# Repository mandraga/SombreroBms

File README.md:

# SombreroBms

SombreroBMS could have been a battery management system board and software for small electric vehicles and conversions. Mainly 36V and 48V battery packs for golf carts.
Currently an unfinished project. Reading the sensors worked and monitoring from a serial line worked. The repository has a simulation project in order to try different balancing algorithms.

Planed features:

- Lithium phosphate battery packs.
- Protection relay to connect to a power relays like a Gigavac 250A.
- State of charge updated by a current sensor during the discharge.
- Custom gauge connected with one wire + Gnd serial communication.
- Monitoring from a laptop computer using a serial communication over USB.
- Passive balancing (possibility for a heavy duty version for first balancing use).
- Undervoltage events count per battery + worst value recording.
- Powered from the battery pack.
- 10 to 18 batteries.

The development was interrupted when I moved to Lyon in 2016. And the client switched to Orion BMS, so the target was lost and the funding shorted.
However I started SombreroBMS2, simpler, safer, cheaper and easier to use. For lighter vehicles (but it will keep the same functionnality).
I will add more unit testing and simulation on it (hence the switch to gitlab). Building more on software interfaces and abstraction layers and using the test driven development aproach.
On the second version the client is myself :)

https://gitlab.com/arenyp/sombrerobms2
http://blog.vreemdelabs.com/

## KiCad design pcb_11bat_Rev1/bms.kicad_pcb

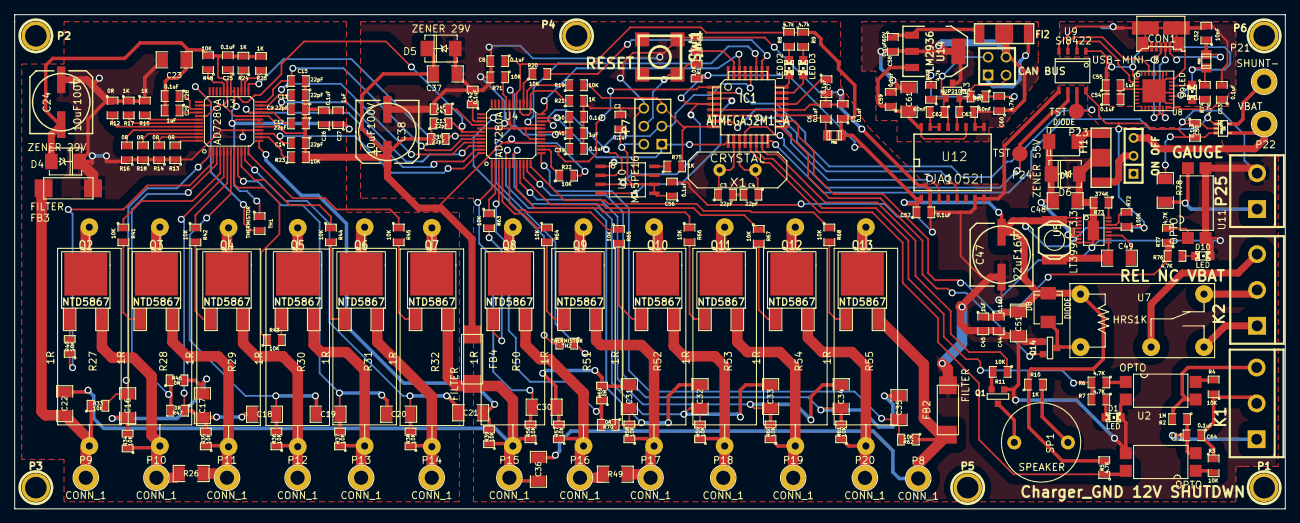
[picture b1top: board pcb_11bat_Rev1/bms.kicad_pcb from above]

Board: 2 copper layers, 180.0 x 70.0 mm, 225 parts (0 on the bottom side), 171 nets.

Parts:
C1, C2, C5, C6, C7, C8, C25, C26, C28, C39, C40, C42, C44, C50, C53, C54, C56, C57, C59, C64: 0.1uF; SM0805
C3, C4, C9, C10, C11, C12, C13, C14, C15: 22pF; SM0805
C16, C17, C18, C19, C20, C21, C30, C31, C32, C33, C34, C35: 0.1uF50V; SM1206
C22, C23, C36, C37: 0.1uF100V; SM1206
C24, C38: 10uF100V; SMDHD/VF
C27, C29, C41, C43, C45, C55: 1uF; SM0805
C47: 22uF16V; SMDHD/VF
C48: 2.2uF100V; SM1206
C49: 0.22uF100V; SM1206
C51: 10uF20V; SM1206POL
C52: 10nF; SM0805
C58: 0.1uF60V; SM0805
C60: 4,7nF; SM0805
C61: 3uF; SM1206
C62, C63: 60nF; SM0805
CAN BUS: CONN_4; PIN_ARRAY_2X2
CON1: USB-MINI-B; MICRO_USB_B
D1, D2, D3, D9, D10: LED; LED-0805
D4, D5: ZENER 29V; DO-214AA(SMB)
D6: ZENER 55V; DO-214AA(SMB)
D7, D8: DIODE; DO_214AA
FB1, FB5: FILTER; c_0805
FB2, FB3, FB4: FILTER; FILTER_NFE61HT102F
FI1, FI2: EMI_FILTER2; EMI_FILTER_NFE61HT
IC1: ATMEGA32M1-A; TQFP32
K1: Charger_GND 12V SHUTDWN; bornier3
K2: REL NC VBAT; bornier3
L1: 33µH; inductor-coilcraft-DS1608
ON OFF: SWITCH_INV; MICROSWITCH_SPST
P1, P2, P3, P4, P5, P6: CONN_1; 1pin
P7: CONN_3X2; pin_array_3x2
P8, P9, P10, P11, P12, P13, P14, P15, P16, P17, P18, P19, P20: CONN_1; 1pin2mm
P21: SHUNT-; 1pin2mm
P22: VBAT; 1pin2mm
P23, P24: TST; TestP
P25: GAUGE; bornier2
Q1, Q14: BC850; SOT23EBC
Q2, Q3, Q4, Q5, Q6, Q7, Q8, Q9, Q10, Q11, Q12, Q13: NTD5867; DPAK2
R1, R3, R4, R11, R19, R20, R22, R23, R33, R34, R35, R36, R37, R38, R39, R40, R41, R42, R43, R44, R45, R48, R56, R57, R58, R59, R60, R61, R62, R63, R64, R65, R66, R67, R68, R71: 10K; SM0805
R2: 1M; SM0805
R5, R6, R7: 4.7K; SM0805
R8, R9: 4.7k; SM0805
R10, R15, R17, R21, R24, R25, R75: 1K; SM0805
R12, R13, R14, R16, R18, R46, R47, R69, R70: 0R; SM0805
R26, R49: 0R; SM1206
R27, R28, R29, R30, R31, R32, R50, R51, R52, R53, R54, R55: 1R; POW_RES
R72: 100K; SM0805
R73: 374K; SM0805
R74, R76, R77: 4,7K; SM0805
R78: 10K; SM1206
R79, R80: 4,7k; SM0805
SP1: SPEAKER; buzzer
SW1: RESET; CMSSW
TH1, TH2: THERMISTOR; SM0805
U1, U2, U11: OPTO; OPTO_CMS
U3, U4: AD7280A; LQFP48
U5: LT3990-3.3; MSOP16E
U6: INA197; sot323-5
U7: HRS1K; REL_PE014
U8: FT232RQ; QFN32-5x5
U9: SI8422; NSOP8
U10: M45PE16; SO8W
U12: TJA1052I; SO16W
U13: NUP2105L; SOT23
U14: LM2936; SOT223
X1: CRYSTAL; HC-18UV

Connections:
/AD7280A/AD7280A_SUB_HI/ALERT: R24.1, U3.27
/AD7280A/AD7280A_SUB_HI/ALERT_IO: C13.2, U3.28, U4.42
/AD7280A/AD7280A_SUB_HI/ALERThi: R15.2, U3.42
/AD7280A/AD7280A_SUB_HI/CB1: R45.1, U3.12
/AD7280A/AD7280A_SUB_HI/CB2: R44.1, U3.10
/AD7280A/AD7280A_SUB_HI/CB3: R43.1, U3.8
/AD7280A/AD7280A_SUB_HI/CB4: R42.1, U3.6
/AD7280A/AD7280A_SUB_HI/CB5: R41.1, U3.4
/AD7280A/AD7280A_SUB_HI/CB6: R40.1, U3.2
/AD7280A/AD7280A_SUB_HI/CNVST/: C15.1, U3.24, U4.44
/AD7280A/AD7280A_SUB_HI/CNVSThi/: R12.2, U3.44
/AD7280A/AD7280A_SUB_HI/CRef: C28.1, U3.39
/AD7280A/AD7280A_SUB_HI/CS/: C12.2, U3.21, U4.47
/AD7280A/AD7280A_SUB_HI/CShi/: R14.2, U3.47
/AD7280A/AD7280A_SUB_HI/HIBAT: C22.1, FB3.1, P9.1, R27.1, R33.1
/AD7280A/AD7280A_SUB_HI/MASTER: R23.1, U3.14
/AD7280A/AD7280A_SUB_HI/PD/: C14.2, U3.15, U4.48
/AD7280A/AD7280A_SUB_HI/PDhi/: R13.2, U3.48
/AD7280A/AD7280A_SUB_HI/SCLK: C9.2, U3.22, U4.46
/AD7280A/AD7280A_SUB_HI/SCLKhi: R18.2, U3.46
/AD7280A/AD7280A_SUB_HI/SDI: C11.2, U3.23, U4.45
/AD7280A/AD7280A_SUB_HI/SDIhi: R17.2, U3.43
/AD7280A/AD7280A_SUB_HI/SDO: R25.1, U3.26
/AD7280A/AD7280A_SUB_HI/SDOhi: R16.2, U3.45
/AD7280A/AD7280A_SUB_HI/VDDNFILTERED: C23.1, C24.1, D4.2, FB3.2, R12.1, R13.1, R14.1, R15.1, R16.1, R17.1, R18.1, U3.16
/AD7280A/AD7280A_SUB_HI/VDRIVE: C25.1, C26.1, C27.1, TH1.1, U3.18, U3.19, U3.29, U3.30
/AD7280A/AD7280A_SUB_HI/VIN0: C21.2, R39.2, U3.13
/AD7280A/AD7280A_SUB_HI/VIN1: C20.2, C21.1, R38.2, U3.11
/AD7280A/AD7280A_SUB_HI/VIN2: C19.2, C20.1, R37.2, U3.9
/AD7280A/AD7280A_SUB_HI/VIN3: C18.2, C19.1, R36.2, U3.7
/AD7280A/AD7280A_SUB_HI/VIN4: C17.2, C18.1, R35.2, R47.1, U3.5
/AD7280A/AD7280A_SUB_HI/VIN5: R46.1, R47.2, U3.3
/AD7280A/AD7280A_SUB_HI/VIN6: C16.1, R33.2, U3.1
/AD7280A/AD7280A_SUB_HI/VRef: C29.1, U3.40
/AD7280A/AD7280A_SUB_LO/ALERT: R20.1, U4.27
/AD7280A/AD7280A_SUB_LO/ALERT_IO: R21.1, U4.25, U4.28
/AD7280A/AD7280A_SUB_LO/CB1: R68.1, U4.12
/AD7280A/AD7280A_SUB_LO/CB2: R67.1, U4.10
/AD7280A/AD7280A_SUB_LO/CB3: R66.1, U4.8
/AD7280A/AD7280A_SUB_LO/CB4: R65.1, U4.6
/AD7280A/AD7280A_SUB_LO/CB5: R64.1, U4.4
/AD7280A/AD7280A_SUB_LO/CB6: R63.1, U4.2
/AD7280A/AD7280A_SUB_LO/CRef: C42.1, U4.39
/AD7280A/AD7280A_SUB_LO/HIBAT: C22.2, C36.1, FB4.1, P15.1, Q7.3, R39.1, R50.1, R56.1
/AD7280A/AD7280A_SUB_LO/LOBAT: C36.2, FB2.2, P8.1, Q13.3, R62.1
/AD7280A/AD7280A_SUB_LO/MASTER: R22.1, U4.14
/AD7280A/AD7280A_SUB_LO/SDIhi: C10.2, U3.25, U4.43
/AD7280A/AD7280A_SUB_LO/SDO: R19.1, U4.26
/AD7280A/AD7280A_SUB_LO/VDDNFILTERED: C9.1, C10.1, C11.1, C12.1, C13.1, C14.1, C15.2, C23.2, C24.2, C25.2, C26.2, C27.2, C28.2, C29.2, C37.1, C38.1, D4.1, D5.2, FB4.2, R22.2, R23.2, R24.2, R25.2, R48.2, U3.17, U3.20, U3.31, U3.41, U4.16
/AD7280A/AD7280A_SUB_LO/VIN0: C35.2, R62.2, U4.13
/AD7280A/AD7280A_SUB_LO/VIN1: C34.2, C35.1, R61.2, U4.11
/AD7280A/AD7280A_SUB_LO/VIN2: C33.2, C34.1, R60.2, U4.9
/AD7280A/AD7280A_SUB_LO/VIN3: C32.2, C33.1, R59.2, U4.7
/AD7280A/AD7280A_SUB_LO/VIN4: C31.2, C32.1, R58.2, R70.1, U4.5
/AD7280A/AD7280A_SUB_LO/VIN5: R69.1, R70.2, U4.3
/AD7280A/AD7280A_SUB_LO/VIN6: C30.1, R56.2, U4.1
/AD7280A/AD7280A_SUB_LO/VREG: C39.1, C40.1, C41.1, TH2.1, U4.18, U4.19, U4.30
/AD7280A/AD7280A_SUB_LO/VRef: C43.1, U4.40
/AD7280A/ALERT: IC1.26, R20.2
/AD7280A/CNVST/: IC1.30, U4.24
/AD7280A/CS/: IC1.27, U4.21
/AD7280A/PD/: IC1.1, U4.15
/AD7280A/SDI: IC1.9, P7.1, U4.23, U10.1
/AD7280A/SDO: IC1.8, P7.5, R19.2, R75.2
/BUZZER: IC1.15, R11.1
/CHARGER_12V: C64.1, K1.2, R3.1, R4.1
/CHARGER_GND: C64.2, K1.1, R2.1, U1.2
/CHARGER_ON/: IC1.13, R5.1, U1.4
/CLK1: C3.1, IC1.10, X1.2
/CLK2: C4.1, IC1.11, X1.1
/CSense/CSENSE: IC1.16, U6.1
/CSense/SHUNT-: P21.1, U6.5
/CSense/VBAT: ON OFF.3, P22.1, U6.4
/Gauge/GAUGEOUT: IC1.18, R76.1, R77.1
/Gauge/GaugeValue: P25.1, R78.2, U11.4
/Isolated_CAN/BMSCANRX: IC1.7, U12.5
/Isolated_CAN/BMSCANTX: IC1.6, U12.3
/Isolated_CAN/BMSGND: C1.2, C2.2, C3.2, C4.2, C5.2, C6.2, C7.2, C8.2, C37.2, C38.2, C39.2, C40.2, C41.2, C42.2, C43.2, C44.2, C45.2, C47.2, C48.2, C50.1, C51.2, C56.2, C57.2, D1.2, D5.1, D6.1, D10.2, FB2.1, FI1.2, IC1.5, IC1.20, P7.6, P25.2, Q1.2, Q14.2, R21.2, R71.2, R73.2, SW1.2, U1.3, U2.2, U4.17, U4.20, U4.31, U4.41, U5.8, U5.17, U6.2, U9.5, U10.7, U11.2, U11.3, U12.2, U12.7, U12.8
/Isolated_CAN/CAN12V: C58.1, FI2.1, U14.1
/Isolated_CAN/CANGND: C58.2, C59.2, C60.1, C61.2, C62.2, C63.1, CAN BUS.4, FI2.2, U12.9, U12.10, U12.14, U12.15, U13.3, U14.2, U14.4
/Isolated_CAN/CANH: C62.1, CAN BUS.2, R79.1, U12.13, U13.1
/Isolated_CAN/CANL: C63.2, CAN BUS.3, R80.2, U12.12, U13.2
/Isolated_CAN/CANUNFILTERED12V: CAN BUS.1, FI2.3
/Isolated_CAN/CANVDD: C59.1, C61.1, U12.11, U12.16, U14.3
/LEDBALANCING: D3.2, IC1.23
/LEDERROR: D2.2, IC1.24
/RESET/: C1.1, IC1.31, P7.4, R1.1, SW1.1
/SPI Flash/CLK: IC1.28, P7.3, U4.22, U10.2
/SPI Flash/CSFLASH/: IC1.3, U10.4
/SPI Flash/FSDO: R75.1, U10.8
/STOP_CHARGE: K1.3, R2.2, U2.3
/STOP_CHARGER: IC1.14, R6.2, R7.2
/VREG/3.3V: C2.1, C5.1, C8.1, C44.1, C45.1, C47.1, C50.2, C51.1, C56.1, C57.1, D8.2, FB1.2, IC1.4, L1.1, P7.2, R1.2, R5.2, R8.1, R9.1, R10.1, R72.1, R78.1, U4.29, U5.1, U5.2, U5.13, U6.3, U7.1, U9.8, U10.3, U10.5, U10.6, U12.1
/VREG/PG: R72.2, U5.14
/VREG/SW: C49.2, L1.2, U5.9
/VREG/VIN: C48.1, D6.2, D7.2, U5.4, U5.6
/comandsolenoid/COILON: IC1.17, Q14.1
/comandsolenoid/StartCOIL: K2.1, U7.4
/comandsolenoid/VbatCOIL: K2.3, U7.3
/usbserial/3V3OUT: C53.1, U8.16
/usbserial/RXD: IC1.12, P24.1, U9.6
/usbserial/TXD: IC1.2, P23.1, U9.7
/usbserial/USBGND: C52.2, C53.2, C54.2, C55.2, CON1.5, CON1.6, CON1.7, CON1.8, CON1.9, U8.4, U8.17, U8.20, U8.24, U8.26, U8.33, U9.4
/usbserial/USBVCC: C54.1, C55.1, FB5.2, R74.1, U8.1, U8.19, U9.1
unnamed: R10.2, SP1.1
unnamed: Q1.3, SP1.2
unnamed: Q1.1, R11.2
unnamed: D3.1, R9.2
unnamed: D2.1, R8.2
unnamed: C7.1, IC1.21
unnamed: D1.1, R7.1
unnamed: R3.2, U1.1
unnamed: R6.1, U2.1
unnamed: C6.1, FB1.1, IC1.19
unnamed: R4.2, U2.4
unnamed: C49.1, U5.11
unnamed: FI1.3, ON OFF.2
unnamed: R73.1, U5.16
unnamed: D7.1, FI1.1
unnamed: K2.2, U7.5
unnamed: D8.1, Q14.3, U7.2
unnamed: D9.2, U8.22
unnamed: CON1.3, U8.14
unnamed: CON1.2, U8.15
unnamed: C52.1, CON1.1, FB5.1
unnamed: D9.1, R74.2
unnamed: U8.30, U9.3
unnamed: U8.2, U9.2
unnamed: D10.1, R76.2
unnamed: R77.2, U11.1
unnamed: C60.2, R79.2, R80.1
unnamed: R48.1, U3.32
unnamed: TH1.2, U3.38
unnamed: Q5.1, R43.2
unnamed: P13.1, Q5.3, R31.1, R37.1
unnamed: Q5.2, R30.2
unnamed: Q4.1, R42.2
unnamed: P12.1, Q4.3, R30.1, R36.1
unnamed: Q4.2, R29.2
unnamed: Q7.1, R45.2
unnamed: Q7.2, R32.2
unnamed: Q6.1, R44.2
unnamed: P14.1, Q6.3, R32.1, R38.1
unnamed: Q6.2, R31.2
unnamed: Q2.2, R27.2
unnamed: Q3.2, R28.2
unnamed: P11.1, Q3.3, R26.2, R29.1, R35.1
unnamed: Q3.1, R41.2
unnamed: Q2.1, R40.2
unnamed: C16.2, C17.1, R34.2, R46.2
unnamed: P10.1, Q2.3, R26.1, R28.1, R34.1
unnamed: R71.1, U4.32
unnamed: TH2.2, U4.38
unnamed: Q13.1, R68.2
unnamed: Q12.1, R67.2
unnamed: Q11.1, R66.2
unnamed: Q10.1, R65.2
unnamed: Q9.1, R64.2
unnamed: Q8.1, R63.2
unnamed: Q9.2, R51.2
unnamed: Q10.2, R52.2
unnamed: P18.1, Q10.3, R53.1, R59.1
unnamed: Q11.2, R53.2
unnamed: Q8.2, R50.2
unnamed: P19.1, Q11.3, R54.1, R60.1
unnamed: Q12.2, R54.2
unnamed: P20.1, Q12.3, R55.1, R61.1
unnamed: Q13.2, R55.2
unnamed: C30.2, C31.1, R57.2, R69.2
unnamed: P16.1, Q8.3, R49.1, R51.1, R57.1
unnamed: P17.1, Q9.3, R49.2, R52.1, R58.1

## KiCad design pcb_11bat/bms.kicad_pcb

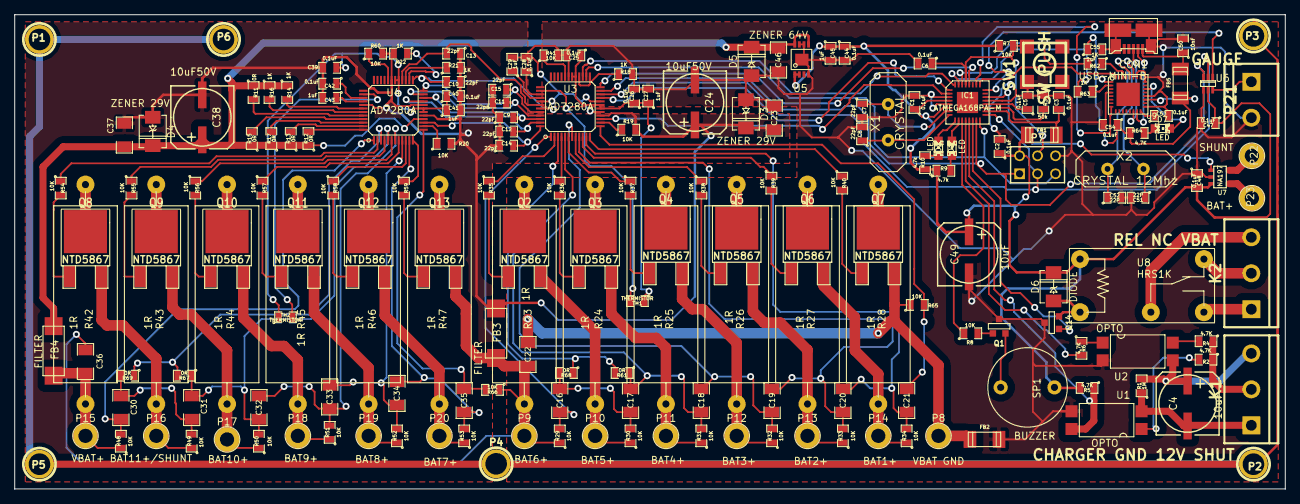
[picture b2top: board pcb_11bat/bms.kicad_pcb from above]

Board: 2 copper layers, 179.5 x 67.0 mm, 192 parts (0 on the bottom side), 152 nets.

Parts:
C1, C2, C3, C5, C6, C25, C26, C28, C39, C40, C42, C44, C47, C48, C53, C54: 0.1uF; SM0805
C4, C49: 10uF; SMDHD/VF
C7, C8, C9, C10, C11, C12, C13, C14, C15: 22pF; SM0805
C16, C17, C18, C19, C20, C21, C22, C23, C30, C31, C32, C33, C34, C35, C36, C37: 0.1uF50V; SM1206
C24, C38: 10uF50V; SMDHD/VF
C27, C29, C41, C43, C45, C55: 1uF; SM0805
C46: 1uF50V; SM1206
C50: 10nF; SM0805
C51, C52: 22P; SM0805
CON1: USB-MINI-B; MICRO_USB_B
D1, D2, D7: LED; LED-0805
D3, D4: ZENER 29V; DO-214AA(SMB)
D5: ZENER 64V; DO-214AA(SMB)
D6: DIODE; DO-214AA(SMB)
FB1, FB2, FB5: FILTER; c_1808
FB3, FB4: FILTER; FILTER_NFE61HT102F
IC1: ATMEGA168PA-M; QFN32
K1: CHARGER GND 12V SHUT; bornier3
K2: REL NC VBAT; bornier3
P1, P2, P3, P4, P5, P6: CONN_1; 1pin
P7: CONN_3X2; pin_array_3x2
P8: VBAT GND; 1pin2mm
P9: BAT6+; 1pin2mm
P10: BAT5+; 1pin2mm
P11: BAT4+; 1pin2mm
P12: BAT3+; 1pin2mm
P13: BAT2+; 1pin2mm
P14: BAT1+; 1pin2mm
P15: VBAT+; 1pin2mm
P16: BAT11+/SHUNT; 1pin2mm
P17: BAT10+; 1pin2mm
P18: BAT9+; 1pin2mm
P19: BAT8+; 1pin2mm
P20: BAT7+; 1pin2mm
P21: GAUGE; bornier2
P22: SHUNT; 1pin2mm
P23: BAT+; 1pin2mm
Q1, Q14: BC550; SOT23EBC
Q2, Q3, Q4, Q5, Q6, Q7, Q8, Q9, Q10, Q11, Q12, Q13: NTD5867; DPAK2
R1: 1M; SM0805
R2, R4, R5, R6: 4.7K; SM0805
R3: 50k; SM0805
R7, R8, R19, R20, R29, R30, R31, R32, R33, R34, R35, R36, R37, R38, R39, R40, R41, R48, R49, R50, R51, R52, R53, R54, R55, R56, R57, R58, R59, R60, R65, R66: 10K; SM0805
R9, R10: 4.7k; SM0805
R11, R12, R13, R15, R17, R61, R67, R68, R69: 0R; SM0805
R14, R16, R18, R21, R22, R62, R63: 1K; SM0805
R23, R24, R25, R26, R27, R28, R42, R43, R44, R45, R46, R47: 1R; POW_RES
R64: 4,7K; SM0805
SP1: BUZZER; buzzer
SW1: SW_PUSH; CMSSW
TH1, TH2: THERMISTOR; SM0805
U1, U2: OPTO; OPTO_CMS
U3, U4: AD7280A; LQFP48
U5: LT3010-5; MSOP8E
U6: LTC2630; SC6
U7: INA197; SOT23-5
U8: HRS1K; REL_PE014
U9: FT232RQ; QFN32-5x5
X1: CRYSTAL; HC-18UV
X2: CRYSTAL 12Mhz; HC-18UV

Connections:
/AD7280A/AD7280A_SUB_HI/ALERT: R21.1, U4.27
/AD7280A/AD7280A_SUB_HI/ALERT_IO: C13.2, U3.42, U4.28
/AD7280A/AD7280A_SUB_HI/ALERThi: R14.2, U4.42
/AD7280A/AD7280A_SUB_HI/AO5.2V: C39.1, C40.1, C41.1, TH2.1, U4.18, U4.19, U4.29, U4.30
/AD7280A/AD7280A_SUB_HI/CB1: R59.1, U4.12
/AD7280A/AD7280A_SUB_HI/CB2: R58.1, U4.10
/AD7280A/AD7280A_SUB_HI/CB3: R57.1, U4.8
/AD7280A/AD7280A_SUB_HI/CB4: R56.1, U4.6
/AD7280A/AD7280A_SUB_HI/CB5: R55.1, U4.4
/AD7280A/AD7280A_SUB_HI/CB6: R54.1, U4.2
/AD7280A/AD7280A_SUB_HI/CNVST/: C15.1, U3.44, U4.24
/AD7280A/AD7280A_SUB_HI/CNVSThi/: R11.2, U4.44
/AD7280A/AD7280A_SUB_HI/CRef: C42.1, U4.39
/AD7280A/AD7280A_SUB_HI/CS/: C12.2, U3.47, U4.21
/AD7280A/AD7280A_SUB_HI/CShi/: R13.2, U4.47
/AD7280A/AD7280A_SUB_HI/HIBAT: C36.1, FB4.1, P15.1, R42.1, R48.1
/AD7280A/AD7280A_SUB_HI/MASTER: R20.1, U4.14
/AD7280A/AD7280A_SUB_HI/PD/: C14.2, U3.48, U4.15
/AD7280A/AD7280A_SUB_HI/PDhi/: R12.2, U4.48
/AD7280A/AD7280A_SUB_HI/SCLK: C9.2, U3.46, U4.22
/AD7280A/AD7280A_SUB_HI/SCLKhi: R17.2, U4.46
/AD7280A/AD7280A_SUB_HI/SDI: C11.2, U3.45, U4.23
/AD7280A/AD7280A_SUB_HI/SDIhi: R16.2, U4.43
/AD7280A/AD7280A_SUB_HI/SDO: R22.1, U4.26
/AD7280A/AD7280A_SUB_HI/SDOhi: R15.2, U4.45
/AD7280A/AD7280A_SUB_HI/VIN0: C35.2, R66.2, U4.13
/AD7280A/AD7280A_SUB_HI/VIN1: C34.2, C35.1, R53.2, U4.11
/AD7280A/AD7280A_SUB_HI/VIN2: C33.2, C34.1, R52.2, U4.9
/AD7280A/AD7280A_SUB_HI/VIN3: C32.2, C33.1, R51.2, U4.7
/AD7280A/AD7280A_SUB_HI/VIN4: C31.2, C32.1, R50.2, R67.1, U4.5
/AD7280A/AD7280A_SUB_HI/VIN5: R67.2, R69.1, U4.3
/AD7280A/AD7280A_SUB_HI/VIN6: C30.1, R48.2, U4.1
/AD7280A/AD7280A_SUB_HI/VRef: C43.1, U4.40
/AD7280A/AD7280A_SUB_LOW/ALERT_IO: R18.1, U3.25, U3.28
/AD7280A/AD7280A_SUB_LOW/AO5.2V: C25.1, C26.1, C27.1, TH1.1, U3.18, U3.19, U3.29, U3.30
/AD7280A/AD7280A_SUB_LOW/CB1: R40.1, U3.12
/AD7280A/AD7280A_SUB_LOW/CB2: R39.1, U3.10
/AD7280A/AD7280A_SUB_LOW/CB3: R38.1, U3.8
/AD7280A/AD7280A_SUB_LOW/CB4: R37.1, U3.6
/AD7280A/AD7280A_SUB_LOW/CB5: R36.1, U3.4
/AD7280A/AD7280A_SUB_LOW/CB6: R35.1, U3.2
/AD7280A/AD7280A_SUB_LOW/CRef: C28.1, U3.39
/AD7280A/AD7280A_SUB_LOW/HIBAT: C22.1, C36.2, FB3.1, P9.1, Q13.3, R23.1, R29.1, R66.1
/AD7280A/AD7280A_SUB_LOW/LOBAT: C22.2, FB2.2, P8.1, Q7.3, R65.1
/AD7280A/AD7280A_SUB_LOW/MASTER: R19.1, U3.14
/AD7280A/AD7280A_SUB_LOW/SDIhi: C10.2, U3.43, U4.25
/AD7280A/AD7280A_SUB_LOW/VDDNFILTERED: C9.1, C10.1, C11.1, C12.1, C13.1, C14.1, C15.2, C23.1, C24.1, C37.2, C38.2, C39.2, C40.2, C41.2, C42.2, C43.2, D3.2, D4.1, FB3.2, R19.2, R20.2, R21.2, R22.2, R60.2, U3.16, U4.17, U4.20, U4.31, U4.41
/AD7280A/AD7280A_SUB_LOW/VIN0: C21.2, R65.2, U3.13
/AD7280A/AD7280A_SUB_LOW/VIN1: C20.2, C21.1, R34.2, U3.11
/AD7280A/AD7280A_SUB_LOW/VIN2: C19.2, C20.1, R33.2, U3.9
/AD7280A/AD7280A_SUB_LOW/VIN3: C18.2, C19.1, R32.2, U3.7
/AD7280A/AD7280A_SUB_LOW/VIN4: C17.2, C18.1, R31.2, R61.1, U3.5
/AD7280A/AD7280A_SUB_LOW/VIN5: R61.2, R68.1, U3.3
/AD7280A/AD7280A_SUB_LOW/VIN6: C16.1, R29.2, U3.1
/AD7280A/AD7280A_SUB_LOW/VRef: C29.1, U3.40
/AD7280A/ALERT: IC1.32, U3.27
/AD7280A/CNVST/: IC1.28, U3.24
/AD7280A/CS/: IC1.1, U3.21
/AD7280A/GND: C1.2, C2.2, C3.2, C5.2, C6.2, C7.2, C8.2, C23.2, C24.2, C25.2, C26.2, C27.2, C28.2, C29.2, C44.2, C45.2, C46.2, C47.2, C48.1, C49.2, C50.2, C51.2, C52.2, C53.2, C54.2, C55.2, CON1.5, CON1.6, CON1.7, CON1.8, CON1.9, D3.1, D5.1, FB2.1, IC1.3, IC1.5, IC1.21, P7.6, P21.2, Q1.3, Q14.3, R3.1, R18.2, R41.2, SW1.2, U1.3, U2.2, U3.17, U3.20, U3.31, U3.41, U5.4, U5.6, U5.7, U5.9, U6.4, U7.2, U9.4, U9.17, U9.20, U9.24, U9.26
/AD7280A/PD/: IC1.2, U3.15
/AD7280A/SCLK: IC1.17, P7.3, U3.22, U6.2
/AD7280A/SDI: IC1.15, P7.1, U3.23, U6.3
/AD7280A/SDO: IC1.16, P7.5, U3.26
/AD7280A/VBAT: C37.1, C38.1, C46.1, D4.2, D5.2, FB4.2, R11.1, R12.1, R13.1, R14.1, R15.1, R16.1, R17.1, U4.16, U5.5, U5.8
/BUZZER: IC1.11, R8.1
/CHARGER_12V: K1.2, R2.1, R4.1
/CHARGER_GND: C4.2, K1.1, R1.1, U1.2
/CHARGER_ON/: IC1.13, R5.1, U1.4
/CSense/5V: C1.1, C2.1, C44.1, C45.1, C47.1, C48.2, C49.1, D6.2, FB1.2, IC1.4, IC1.6, P7.2, R5.2, R7.1, R9.1, R10.1, SP1.1, U5.1, U5.2, U6.5, U7.3, U8.1
/CSense/CSENSE: IC1.22, U7.1
/CSense/SHUNT-: P22.1, U7.5
/CSense/SHUNT_VBAT+: P23.1, U7.4
/LEDBALANCING: D2.2, IC1.9
/LEDERROR: D1.2, IC1.10
/RESET/: C6.1, IC1.29, P7.4, R7.2, SW1.1
/SHIELD: P1.1, P2.1, P3.1, P4.1, P5.1, P6.1
/STOP_CHARGE: C4.1, K1.3, R1.2, U2.3
/STOP_CHARGER: IC1.12, R6.2
/comandsolenoid/COILON: IC1.14, Q14.2
/comandsolenoid/StartCOIL: K2.1, U8.4
/comandsolenoid/VbatCOIL: K2.3, U8.3
/gauge/CSDAC/: IC1.24, U6.1
/gauge/GaugeValue: P21.1, U6.6
/usbserial/3V3OUT: C53.1, U9.16
/usbserial/CLEARTOSEND: IC1.26, U9.8
/usbserial/REQUESTTOSEND: IC1.25, U9.32
/usbserial/RXD: IC1.30, R62.2
/usbserial/TXD: IC1.31, R63.2
/usbserial/USBVCC: C54.1, C55.1, FB5.2, R64.1, U9.1, U9.19
unnamed: R6.1, U2.1
unnamed: R4.2, U2.4
unnamed: R2.2, U1.1
unnamed: Q1.1, SP1.2
unnamed: Q1.2, R8.2
unnamed: IC1.19, R3.2
unnamed: C3.1, FB1.1, IC1.18
unnamed: C5.1, IC1.20
unnamed: D2.1, R10.2
unnamed: D1.1, R9.2
unnamed: C7.1, IC1.7, X1.2
unnamed: C8.1, IC1.8, X1.1
unnamed: D6.1, Q14.1, U8.2
unnamed: K2.2, U8.5
unnamed: CON1.2, U9.15
unnamed: CON1.3, U9.14
unnamed: D7.2, U9.22
unnamed: C52.1, U9.28, X2.1
unnamed: R63.1, U9.2
unnamed: R62.1, U9.30
unnamed: C51.1, U9.27, X2.2
unnamed: D7.1, R64.2
unnamed: C50.1, CON1.1, FB5.1
unnamed: Q4.1, R37.2
unnamed: Q4.2, R25.2
unnamed: Q3.1, R36.2
unnamed: P11.1, Q3.3, R25.1, R31.1
unnamed: Q3.2, R24.2
unnamed: Q6.2, R27.2
unnamed: Q5.1, R38.2
unnamed: P13.1, Q5.3, R27.1, R33.1
unnamed: Q5.2, R26.2
unnamed: P12.1, Q4.3, R26.1, R32.1
unnamed: P10.1, Q2.3, R24.1, R30.1
unnamed: Q2.1, R35.2
unnamed: Q2.2, R23.2
unnamed: R41.1, U3.32
unnamed: TH1.2, U3.38
unnamed: Q7.1, R40.2
unnamed: Q7.2, R28.2
unnamed: Q6.1, R39.2
unnamed: P14.1, Q6.3, R28.1, R34.1
unnamed: C16.2, C17.1, R30.2, R68.2
unnamed: TH2.2, U4.38
unnamed: Q13.1, R59.2
unnamed: Q8.1, R54.2
unnamed: Q8.2, R42.2
unnamed: Q11.2, R45.2
unnamed: Q12.1, R58.2
unnamed: Q9.2, R43.2
unnamed: Q9.1, R55.2
unnamed: Q10.2, R44.2
unnamed: Q10.1, R56.2
unnamed: R60.1, U4.32
unnamed: Q13.2, R47.2
unnamed: P20.1, Q12.3, R47.1, R53.1
unnamed: Q12.2, R46.2
unnamed: C30.2, C31.1, R49.2, R69.2
unnamed: P16.1, Q8.3, R43.1, R49.1
unnamed: P17.1, Q9.3, R44.1, R50.1
unnamed: Q11.1, R57.2
unnamed: P18.1, Q10.3, R45.1, R51.1
unnamed: P19.1, Q11.3, R46.1, R52.1

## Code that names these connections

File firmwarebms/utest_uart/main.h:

#define SBI(port, bit) ((port) |= (1 << (bit)))
#define CBI(port, bit) ((port) &= ~(1 << (bit)))

// PORTB
#define CSBAT  PB0
#define BUZZER PB1
#define PD     PB2
#define MOSI   PB3
#define MISO   PB4
#define SCLK   PB5
#define OSC1   PB6
#define OSC2   PB7

// PORTC
#define CNVSTART  PC0
#define NC1       PC1
#define NC2       PC2
#define RTS       PC3
#define CTS       PC4
#define RELON     PC5
#define RESET     PC6

// PORTD
#define RXD           PD0
#define TXD           PD1
#define ALERT         PD2
#define CHARGER_ON    PD3
#define CSDAC         PD4
#define STOP_CHARGER  PD5
#define LED_BALANCING PD6
#define LED_ERROR     PD7

// Main state machine
#define STATE_START    0
#define STATE_CHARGEON 1  // The charger is on
#define STATE_CHARGING 2  // same plus charging
#define STATE_IDLE     3  // Idle, does nothing
#define STATE_RUN      4  // Run, the current is beingused and state of charge updated
#define STATE_RELAX    5  // After run, wait for the battery voltage to spatbilise (lithium behaviour)
#define STATE_SECURITY 6  // Undervoltage or overvoltage or error like trying to start when charging
#define STATE_CURRENT_SECURITY 7  // Over current or too much current during charge
#define STATE_CRITICAL_FAILURE 8  // Stops here, no way to get out but a reset

#define BAUDRATE       9600
#ifndef F_CPU
#define F_CPU       3686000
#endif

void _delay_ms_S(int millisecond);

typedef struct  s_ibat
{
  unsigned long ibat; // milliAmps
  int           timeslice_ms;
}               t_ibat;

// EEPROM data
typedef struct  s_eeprom_data
{
  int           install_date_year;
  char          install_date_month;
  char          install_date_day;
  unsigned long bat_maxv;            // mV
  unsigned long bat_minv;
  int           bat_tmax;            // temperature °C
  int           bat_tmin;
  char          bat_elements;
  int           full_charge;         // AH
  unsigned long full_chargeV;        // mV when the pack voltage reaches this value, the charger is stoped and the charge is set at 100%
  int           max_current;         // Amp
  char          serial_number[10];   //  8 bytes             plus 0 end of string
  char          client[33];          // 32 bytes Client name plus 0 end of string
  // These are often programmed
  int           charge_cycles;
  unsigned long charge_time_minutes; // Total charging time
  int           min_temperature;     // Extreme temperatures °C
  int           max_temperature;
}               t_eeprom_data;

// Per battery eeprom information
typedef struct  s_eeprom_battery
{
  unsigned long lowestV;
  int           lowVevents; // times vbat whent under the treshold before a charge
  unsigned long cap;        // More or less the capacity, or charge speed...
}               t_eeprom_battery;

// Ram data
typedef struct  s_pack_variable_data
{
  unsigned int  uptime_days;
  unsigned int  uptime_minutes;
  unsigned int  tseconds;                 // Tenth of seconds
  int           max_discharge;            // Discharge current in Amperes
  unsigned long c_discharge;              // Discharge, last value mA
  unsigned int  state_of_charge;          // SOC mili Ampere Hour
  unsigned long vbat[MAXBATTERY];         // Batterey milivolts, last value
  unsigned long total_vbat;               // Pack voltage in mv
  int           temperature[MAXMODULES];  // °C
  char          app_state;                // State machine variable
  // Internal variables
  unsigned long c_discharge_accumulator;  // Accumulates mA per hour
  char          charging_started;         // Once started it must finish
  int           charge_time_count_tenth;  // 1/10 second
  int           charge_time_count;        // Minutes
  int           idle_counter;             // Used to get out of the relapse state
  char          prev_idle;                // Used to count the charge cycles
}               t_pack_variable_data;

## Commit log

2015-11-21 Kicad schematics
2015-11-21 Kicad modules n libs
2016-01-03 Component association finished, added/created required modules
2016-01-03 changed wire pins to 2mm holes, mosfet NTD5867 shcematics and filter footprint, created the pcb file for routing
2016-01-04 placement before routing & corrected a missing resitor on vlow
2016-01-05 fixed misplaced caps on the vins, changed some pins assignations on the avr and routed
2016-01-06 sent to production, buzeer pad drill change, changed vias diameter
2016-01-21 Began to work on hte firmware
2016-01-22 added the begin of the state machine
2016-01-22 added a gitignore file
2016-01-23 changed the uart code to custom interrupt based code, and began to work on the rs232 protocol and eeprom writes
2016-01-24 finished to write the serial protocol and eeprom code, starting with the cell readings.
2016-01-25 basic features written, before the battery balancing algorithm
2016-01-25 started the balancing, added temperature and balancing state to the serial data specifications
2016-01-26 added the thermistor code, and finished the basics for battery balancing
2016-01-26 Added missing values to the serial code.
2016-01-27 compiled
2016-01-27 pushed the string constants into program space
2016-01-27 added simulation code and compiled the bootloader
2016-01-28 first working version on the simulator
2016-01-29 balancing works on the simulator
2016-02-08 Soldering components on the prototype, some changes on the schematics and component values
2016-02-11 added PC side FLTX inteface, plus named pipe serial suport to be used in the simulator
2016-02-12 added the serial port tab, untested
2016-02-12 commit just to store the code before returning to scoreview
2016-02-25 changed the board to add an SPI flash and 3V uC power
2016-02-26 added serial port code to the simulator + added a switch on the Vbat power to the uController
2016-02-28 added a serial port thread to the gui
2016-03-05 Improvements on the serial link
2016-03-07 added the Vbat history tab
2016-03-07 Added a CRC
2016-03-08 new balancing and charge functions, gauge schematic
2016-03-09 added a 1K resistor to the buzzer, t's frying
2016-03-09 reduced the hex size to fit in the ATMEGA168pa
2016-03-17 Changed avr-size parameters in the Makefile
2016-03-24 Bugfixes, transistor footprint, bootloader, uart unit test
2016-03-25 Bootloader working with avrdude 6.3
2016-03-25 change to the bootloader led
2016-03-26 changes in flash write of the bootloader
2016-03-30 + flash programing in assembler code
2016-04-04 fixed the bootloader start address (now at end of flash and not in the middle of it)
2016-04-04 added the page flash assembler file
2016-04-04 still an address error on the bot block, works now
2016-04-04 changed the uart test
2016-04-04 added led tests
2016-04-05 test led passed
2016-04-05 sync with stk500v2 bootloader code
2016-04-05 added microcontroler functional tests, change the strncmp and sprintf funtions to take PSTR() strings
2016-04-16 progress on the AD280A commands but must create a new board with an isolator on the usb bus because it fucks with every IO port on the board
2016-04-16 New schematic in 3,3V with 2MB flash, switching regulator, usb data isolation, can bus and bug fixes
2016-04-17 Ready to route the new schematic
2016-05-04 New board sent to proto production
2018-11-08 Changed the status of the project
2018-11-09 More coments
2018-11-09 More edit on the readme
